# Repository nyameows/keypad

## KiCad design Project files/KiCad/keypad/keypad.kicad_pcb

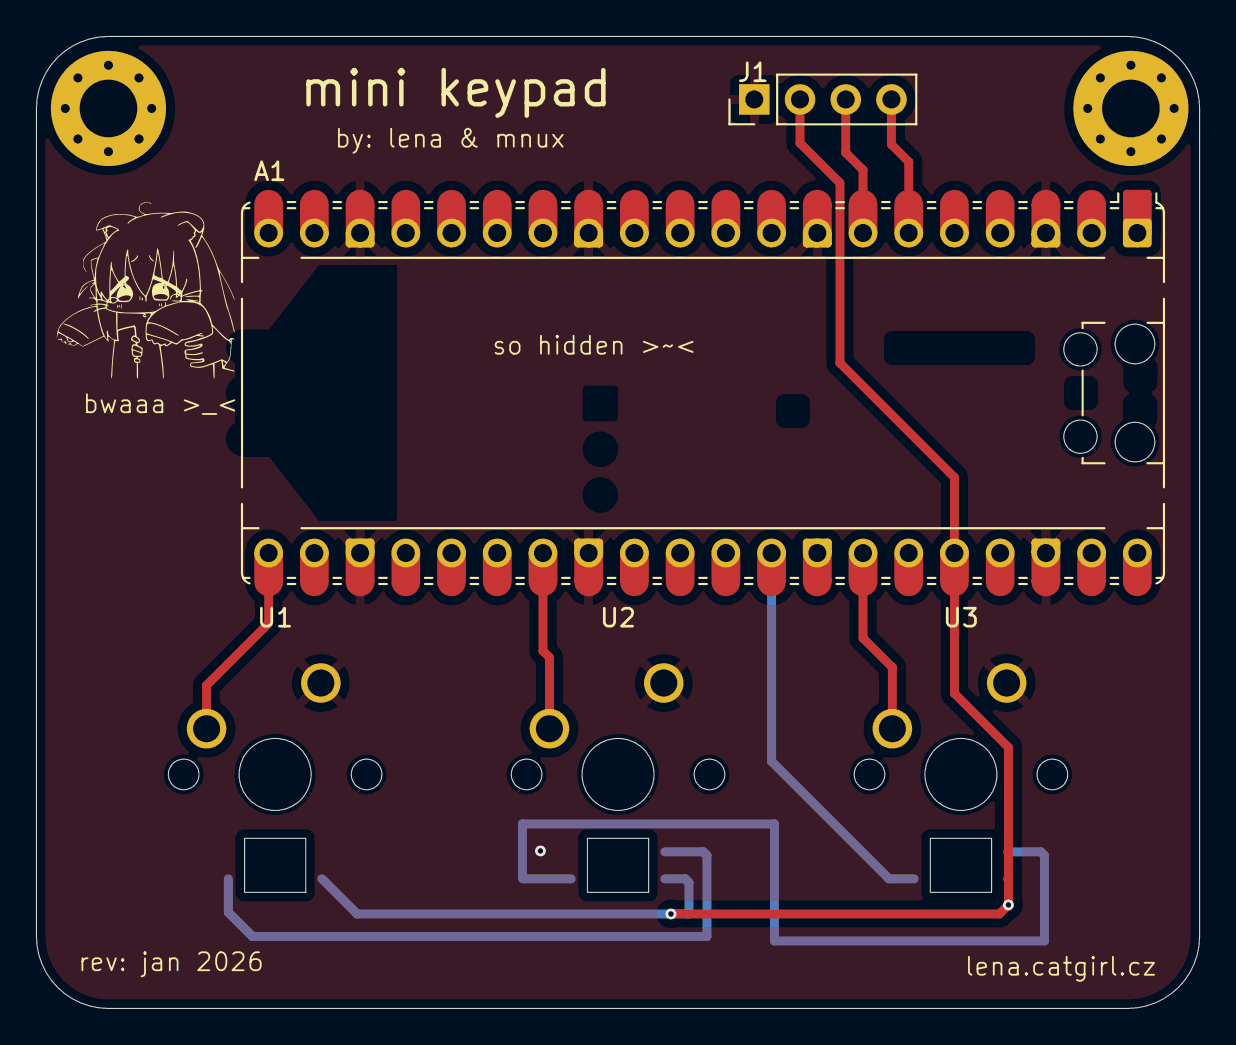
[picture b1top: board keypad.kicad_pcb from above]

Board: 2 copper layers, 64.6 x 54.0 mm, 7 parts (0 on the bottom side), 10 nets.

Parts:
A1: RaspberryPi_Pico; RaspberryPi_Pico_Common_Unspecified
H1, H2: MountingHole_Pad; MountingHole_3.2mm_M3_Pad_Via
J1: Conn_01x04_Pin; PinHeader_1x04_P2.54mm_Vertical
U1, U2, U3: Cherry_MX_RGB; Cherry-MX_PCB-Mounted_LTST-A683CEGBW_Mill-Max-7305

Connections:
+3.3V: A1.36 (3V3), J1.2, U1.4 (VCC), U2.4 (VCC), U3.4 (VCC)
GND: A1.3 (GND), A1.8 (GND), A1.13 (GND), A1.18 (GND), A1.23 (GND), A1.28 (GND), A1.38 (GND), J1.1, U1.1 (GND), U1.6 (SW2), U2.1 (GND), U2.6 (SW2), U3.1 (GND), U3.6 (SW2)
unnamed: A1.21 (GPIO16), U1.5 (SW1)
unnamed: A1.27 (GPIO21), U2.5 (SW1)
unnamed: A1.32 (GPIO27_ADC1), U3.2 (DIN)
unnamed: A1.34 (GPIO28_ADC2), U3.5 (SW1)
unnamed: U1.2 (DIN), U2.3 (DOUT)
unnamed: U2.2 (DIN), U3.3 (DOUT)
scl: A1.7 (GPIO5), J1.3
sda: A1.6 (GPIO4), J1.4

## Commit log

2026-02-15 purr nyaa ><
2026-02-15 freecad
2026-02-15 purr
